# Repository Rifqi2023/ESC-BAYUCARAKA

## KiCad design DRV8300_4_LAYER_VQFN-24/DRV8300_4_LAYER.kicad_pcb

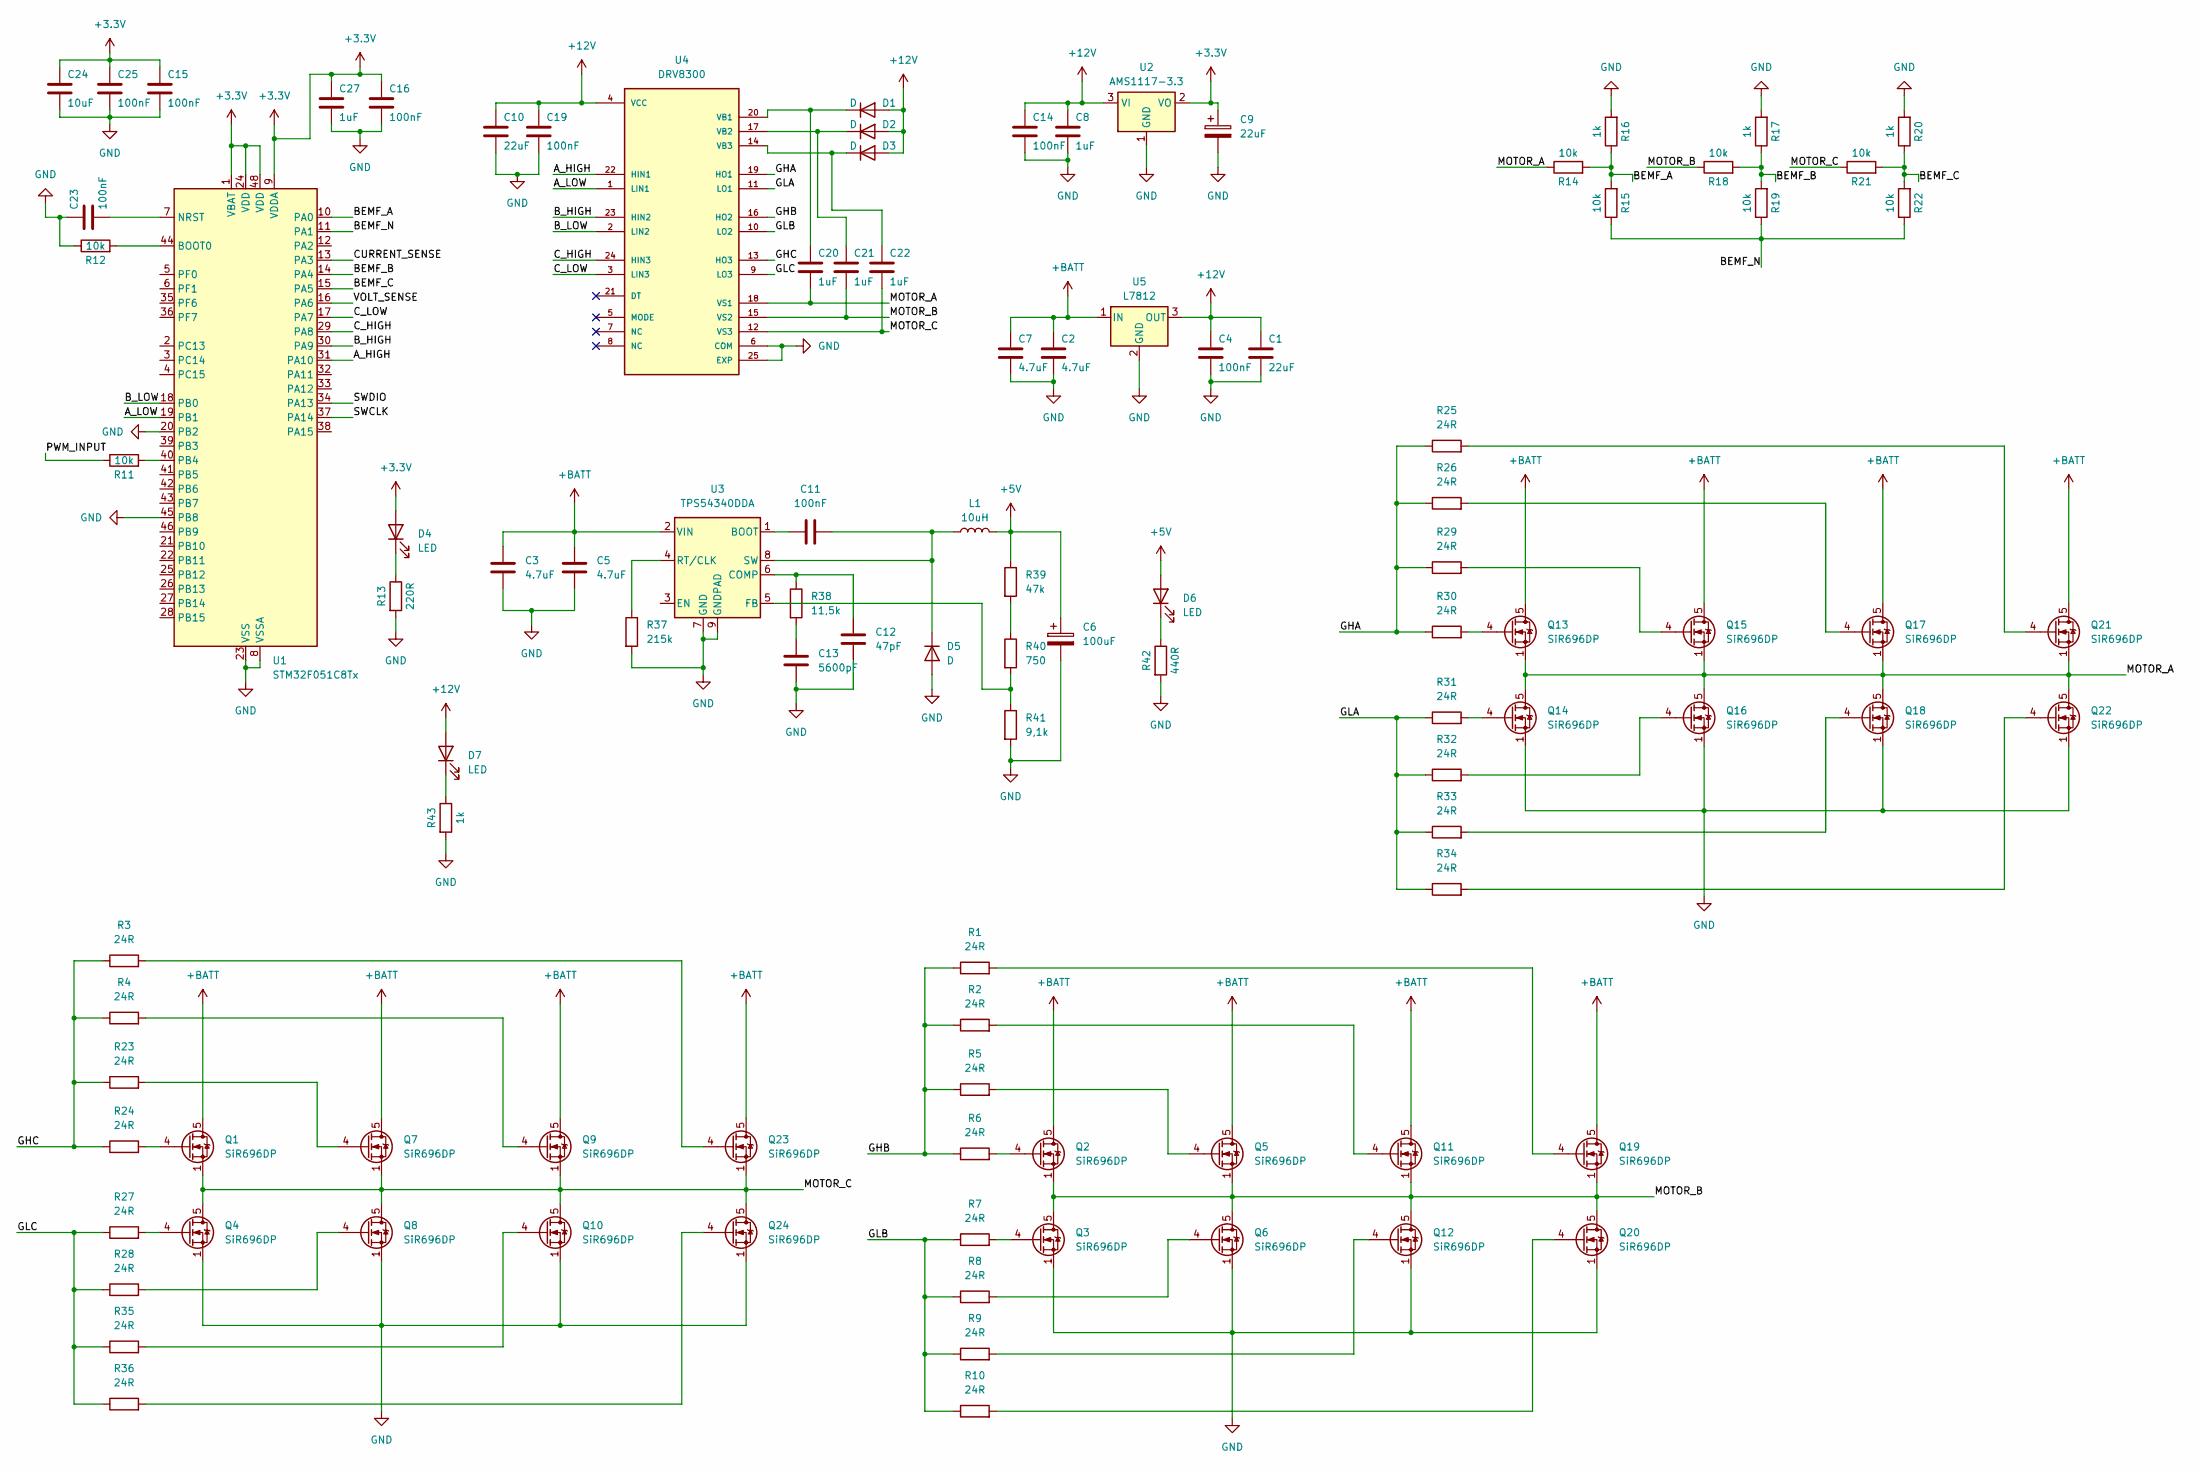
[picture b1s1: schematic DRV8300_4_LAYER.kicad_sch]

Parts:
C1, C10: 22uF; C_0805_2012Metric
C2, C7: 4.7uF; C_0603_1608Metric
C3, C5: 4.7uF; C_1206_3216Metric_Pad1.33x1.80mm_HandSolder
C4, C14, C15, C16, C19, C25: 100nF; C_0603_1608Metric
C6: 100uF; CP_Elec_6.3x7.7
C8, C20, C21, C22, C27: 1uF; C_0603_1608Metric
C9: 22uF; CP_EIA-6032-28_Kemet-C
C11: 100nF; C_0603_1608Metric_Pad1.08x0.95mm_HandSolder
C12: 47pF; C_0603_1608Metric_Pad1.08x0.95mm_HandSolder
C13: 5600pF; C_0603_1608Metric_Pad1.08x0.95mm_HandSolder
C23: 100nF; C_0402_1005Metric
C24: 10uF; C_0805_2012Metric
D1, D2, D3: D; D_0603_1608Metric
D4, D6, D7: LED; LED_0603_1608Metric
D5: D; D_SMC
L1: 10uH; L_TechFuse_SL1040
Q1, Q2, Q3, Q4, Q5, Q6, Q7, Q8, Q9, Q10, Q11, Q12, Q13, Q14, Q15, Q16, Q17, Q18, Q19, Q20, Q21, Q22, Q23, Q24: SiR696DP; PowerPAK_SO-8_Single
R1, R2, R3, R4, R5, R6, R7, R8, R9, R10, R23, R24, R25, R26, R27, R28, R29, R30, R31, R32, R33, R34, R35, R36: 24R; R_0603_1608Metric
R11, R12, R14, R15, R18, R19, R21, R22: 10k; R_0603_1608Metric
R13: 220R; R_0603_1608Metric
R16, R17, R20, R43: 1k; R_0603_1608Metric
R37: 215k; R_0603_1608Metric_Pad0.98x0.95mm_HandSolder
R38: 11,5k; C_0603_1608Metric_Pad1.08x0.95mm_HandSolder
R39: 47k; R_0603_1608Metric_Pad0.98x0.95mm_HandSolder
R40: 750; R_0603_1608Metric_Pad0.98x0.95mm_HandSolder
R41: 9,1k; R_0603_1608Metric_Pad0.98x0.95mm_HandSolder
R42: 440R; R_0603_1608Metric
U1: STM32F051C8Tx; LQFP-48_7x7mm_P0.5mm
U2: AMS1117-3.3; SOT-223-3_TabPin2
U3: TPS54340DDA; Texas_HSOP-8-1EP_3.9x4.9mm_P1.27mm
U4: DRV8300; VQFN-24-1EP_4x4mm_P0.5mm_EP2.5x2.5mm
U5: L7812; TO-252-2

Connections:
+3.3V: C9.1, C15.1, C16.1, C24.1, C25.1, C27.1, D4.2 (A), U1.1 (VBAT), U1.9 (VDDA), U1.24 (VDD), U1.48 (VDD), U2.2 (VO)
+5V: C6.1, D6.2 (A), L1.2, R39.1
+12V: C1.1, C4.1, C8.1, C10.1, C14.1, C19.1, D1.2 (A), D2.2 (A), D3.2 (A), D7.2 (A), U2.3 (VI), U4.4 (VCC), U5.3 (OUT)
+BATT: C2.1, C3.1, C5.1, C7.1, Q1.5 (D), Q2.5 (D), Q5.5 (D), Q7.5 (D), Q9.5 (D), Q11.5 (D), Q13.5 (D), Q15.5 (D), Q17.5 (D), Q19.5 (D), Q21.5 (D), Q23.5 (D), U3.2 (VIN), U5.1 (IN)
/A_HIGH: U1.31 (PA10), U4.22 (HIN1)
/A_LOW: U1.19 (PB1), U4.1 (LIN1)
/BEMF_A: R14.2, R15.2, R16.1, U1.10 (PA0)
/BEMF_B: R17.1, R18.2, R19.2, U1.14 (PA4)
/BEMF_C: R20.1, R21.2, R22.2, U1.15 (PA5)
/BEMF_N: R15.1, R19.1, R22.1, U1.11 (PA1)
/B_HIGH: U1.30 (PA9), U4.23 (HIN2)
/B_LOW: U1.18 (PB0), U4.2 (LIN2)
/CURRENT_SENSE: U1.13 (PA3)
/C_HIGH: U1.29 (PA8), U4.24 (HIN3)
/C_LOW: U1.17 (PA7), U4.3 (LIN3)
/GHA: R25.1, R26.1, R29.1, R30.1, U4.19 (HO1)
/GHB: R1.1, R2.1, R5.1, R6.1, U4.16 (HO2)
/GHC: R3.1, R4.1, R23.1, R24.1, U4.13 (HO3)
/GLA: R31.1, R32.1, R33.1, R34.1, U4.11 (LO1)
/GLB: R7.1, R8.1, R9.1, R10.1, U4.10 (LO2)
/GLC: R27.1, R28.1, R35.1, R36.1, U4.9 (LO3)
/MOTOR_A: C20.2, Q13.1 (S), Q13.2 (S), Q13.3 (S), Q14.5 (D), Q15.1 (S), Q15.2 (S), Q15.3 (S), Q16.5 (D), Q17.1 (S), Q17.2 (S), Q17.3 (S), Q18.5 (D), Q21.1 (S), Q21.2 (S), Q21.3 (S), Q22.5 (D), R14.1, U4.18 (VS1)
/MOTOR_B: C21.2, Q2.1 (S), Q2.2 (S), Q2.3 (S), Q3.5 (D), Q5.1 (S), Q5.2 (S), Q5.3 (S), Q6.5 (D), Q11.1 (S), Q11.2 (S), Q11.3 (S), Q12.5 (D), Q19.1 (S), Q19.2 (S), Q19.3 (S), Q20.5 (D), R18.1, U4.15 (VS2)
/MOTOR_C: C22.2, Q1.1 (S), Q1.2 (S), Q1.3 (S), Q4.5 (D), Q7.1 (S), Q7.2 (S), Q7.3 (S), Q8.5 (D), Q9.1 (S), Q9.2 (S), Q9.3 (S), Q10.5 (D), Q23.1 (S), Q23.2 (S), Q23.3 (S), Q24.5 (D), R21.1, U4.12 (VS3)
/PWM_INPUT: R11.1
/SWCLK: U1.37 (PA14)
/SWDIO: U1.34 (PA13)
/VOLT_SENSE: U1.16 (PA6)
GND: C1.2, C2.2, C3.2, C4.2, C5.2, C6.2, C7.2, C8.2, C9.2, C10.2, C12.1, C13.1, C14.2, C15.2, C16.2, C19.2, C23.1, C24.2, C25.2, C27.2, D5.2 (A), Q3.1 (S), Q3.2 (S), Q3.3 (S), Q4.1 (S), Q4.2 (S), Q4.3 (S), Q6.1 (S), Q6.2 (S), Q6.3 (S), Q8.1 (S), Q8.2 (S), Q8.3 (S), Q10.1 (S), Q10.2 (S), Q10.3 (S), Q12.1 (S), Q12.2 (S), Q12.3 (S), Q14.1 (S), Q14.2 (S), Q14.3 (S), Q16.1 (S), Q16.2 (S), Q16.3 (S), Q18.1 (S), Q18.2 (S), Q18.3 (S), Q20.1 (S), Q20.2 (S), Q20.3 (S), Q22.1 (S), Q22.2 (S), Q22.3 (S), Q24.1 (S), Q24.2 (S), Q24.3 (S), R12.1, R13.2, R16.2, R17.2, R20.2, R37.2, R41.2, R42.2, R43.2, U1.8 (VSSA), U1.20 (PB2), U1.23 (VSS), U1.45 (PB8), U1.47 (VSS), U2.1 (GND), U3.7 (GND), U3.9 (GNDPAD), U4.6 (COM), U4.25 (EXP), U5.2 (GND)
unnamed: C13.2, R38.2
unnamed: C20.1, D1.1 (K), U4.20 (VB1)
unnamed: C21.1, D2.1 (K), U4.17 (VB2)
unnamed: C22.1, D3.1 (K), U4.14 (VB3)
unnamed: D4.1 (K), R13.1
unnamed: C11.2, D5.1 (K), L1.1, U3.8 (SW)
unnamed: D6.1 (K), R42.1
unnamed: D7.1 (K), R43.1
unnamed: Q1.4 (G), R24.2
unnamed: Q2.4 (G), R6.2
unnamed: Q3.4 (G), R7.2
unnamed: Q4.4 (G), R27.2
unnamed: Q5.4 (G), R5.2
unnamed: Q6.4 (G), R8.2
unnamed: Q7.4 (G), R23.2
unnamed: Q8.4 (G), R28.2
unnamed: Q9.4 (G), R4.2
unnamed: Q10.4 (G), R35.2
unnamed: Q11.4 (G), R2.2
unnamed: Q12.4 (G), R9.2
unnamed: Q13.4 (G), R30.2
unnamed: Q14.4 (G), R31.2
unnamed: Q15.4 (G), R29.2
unnamed: Q16.4 (G), R32.2
unnamed: Q17.4 (G), R26.2
unnamed: Q18.4 (G), R33.2
unnamed: Q19.4 (G), R1.2
unnamed: Q20.4 (G), R10.2
unnamed: Q21.4 (G), R25.2
unnamed: Q22.4 (G), R34.2
unnamed: Q23.4 (G), R3.2
unnamed: Q24.4 (G), R36.2
unnamed: R39.2, R40.1
unnamed: R12.2, U1.44 (BOOT0)
unnamed: C23.2, U1.7 (NRST)
unnamed: R11.2, U1.40 (PB4)
unnamed: C11.1, U3.1 (BOOT)
unnamed: C12.2, R38.1, U3.6 (COMP)
unnamed: R40.2, R41.1, U3.5 (FB)
unnamed: R37.1, U3.4 (RT/CLK)

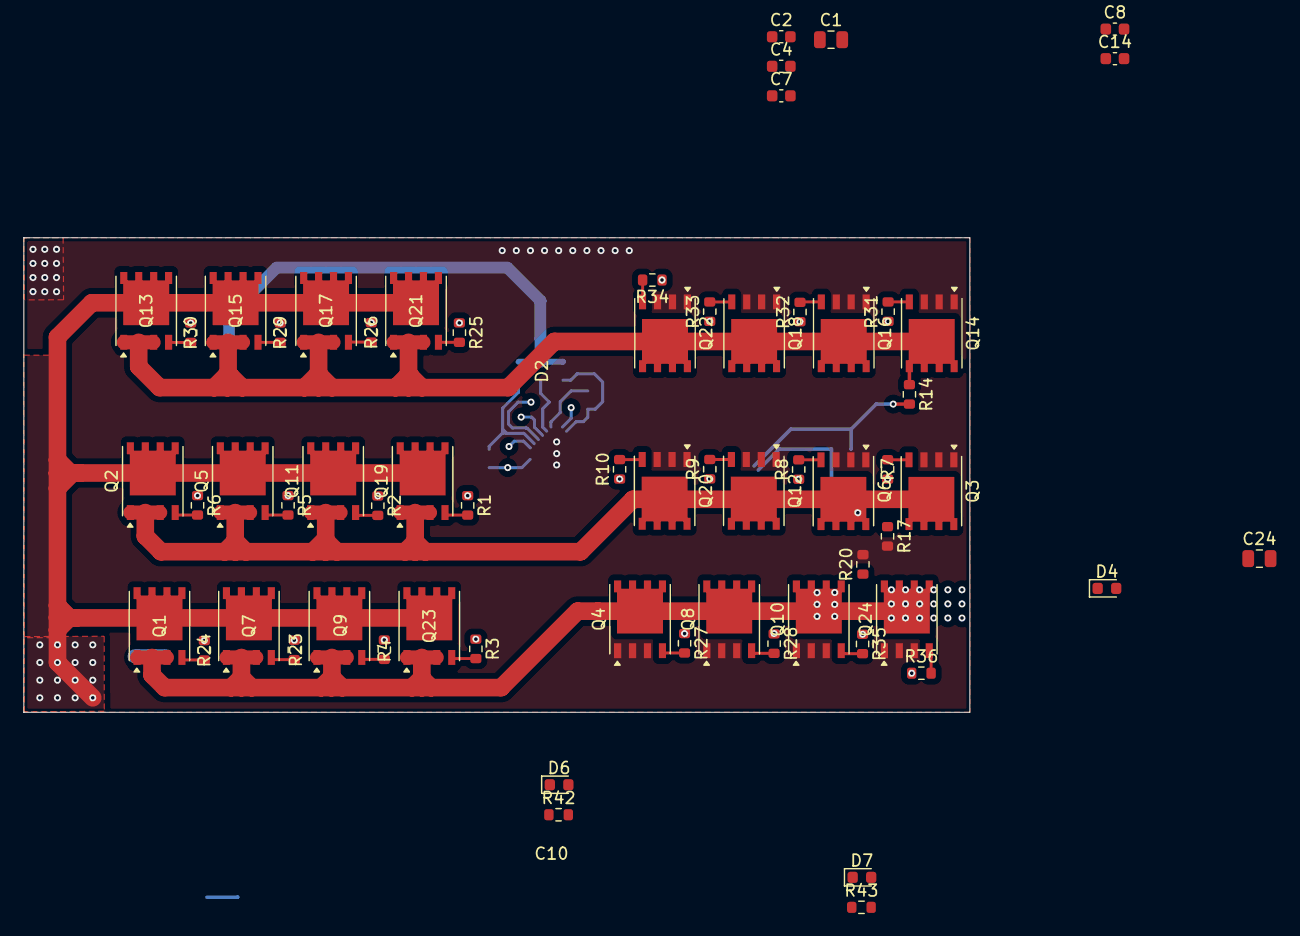
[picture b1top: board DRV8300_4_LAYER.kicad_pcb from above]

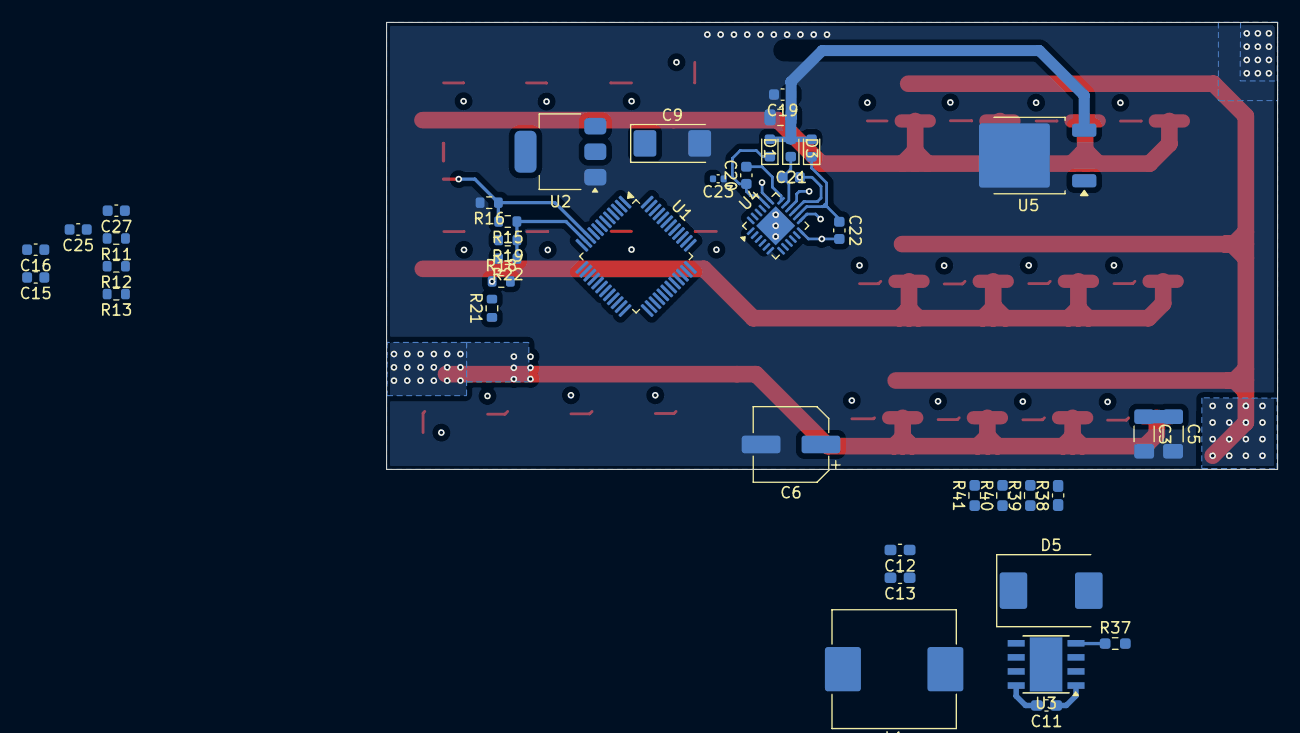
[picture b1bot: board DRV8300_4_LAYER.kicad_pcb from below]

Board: 4 copper layers, 80.4 x 40.3 mm, 104 parts (41 on the bottom side), 64 nets.

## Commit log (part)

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2026-04-17 DRV8300-4-LAYER-VQFN24
2026-04-17 tambahkan folder baru untuk versi drv8300 tssop 20
2026-04-17 TAMBAHAN FOLDER BUAT SIMPEN DRV8300 VERSI TSSOP-20
2026-04-17 GANTI FOLDER
2026-04-18 VQFN-24
2026-04-19 SAVE 19/04/26
